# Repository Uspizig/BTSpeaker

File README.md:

# BTSpeaker: The retrofit Board for an cheap Aliexpress Speaker

## Features:

1. **AudioAmplifier MAX98357**: Listen to your favourite Tunes with an Audio Amplifier

2. **I2C Connector for Sensor**: Connect your favourite I2C Sensor board with the embedded 2.54mm connector

3. **LoRa**: Long Range Communication like Meshtastikm, The Thingsnetwork or Helium

4. **Wireless Control**: Untehther your development process with the wireless capabilities. With WiFi, Lora and BLE, this tool allows remote control and data logging. Users can adjust settings and monitor data from a distance, offering a more flexible development experience.

5. **Open Source & Programmable**: As an open-source device, the Device offers unmatched versatility. It is fully programmable, allowing you to tailor its functionality to your specific applications. This customization extends to software and hardware, opening up endless possibilities for creative and efficient project development.

6. **Compact Design**: Designed for convenience, the LoRaCam Board compact and sleek form factor allows for seamless integration into existing setups. Its compatibility with USB PD power sources and inline integration capability minimizes the need for additional equipment or extensive redesign, making it a versatile and user-friendly addition to any development environment.

7. **Eink/Epaper-Display**: Monitor live the current status

8. **LoRa**: Operate the Device in remote areas without Wifi in Standalone mode

9. **3 x RGB LED**: Status LED
## Specifications

### Key Features:
1. **Audio Player**: Play your favorite tunes from SD Card
2. **Web Radio**: Play your favourite tunes from the Web
3. **RGB LEDs** Illuminate your room with fany colors
4. **GYRO** Monitor movements, steps, pedometer

### Future Developments:

AI Detection of movememt and determine if the device shall sent the data via LoRa 

## Testing for Performance

At the heart of BTSpeaker's design is a commitment to reliability and performance. To ensure that SenseLoRaCam stands up to real-world demands, we subjected it to testing under use conditions.

## License

MIT License

Copyright (c) 2025 blue2monster

Permission is hereby granted, free of charge, to any person obtaining a copy
of this software and associated documentation files (the "Software"), to deal
in the Software without restriction, including without limitation the rights
to use, copy, modify, merge, publish, distribute, sublicense, and/or sell
copies of the Software, and to permit persons to whom the Software is
furnished to do so, subject to the following conditions:

The above copyright notice and this permission notice shall be included in all
copies or substantial portions of the Software.

THE SOFTWARE IS PROVIDED "AS IS", WITHOUT WARRANTY OF ANY KIND, EXPRESS OR
IMPLIED, INCLUDING BUT NOT LIMITED TO THE WARRANTIES OF MERCHANTABILITY,
FITNESS FOR A PARTICULAR PURPOSE AND NONINFRINGEMENT. IN NO EVENT SHALL THE
AUTHORS OR COPYRIGHT HOLDERS BE LIABLE FOR ANY CLAIM, DAMAGES OR OTHER
LIABILITY, WHETHER IN AN ACTION OF CONTRACT, TORT OR OTHERWISE, ARISING FROM,
OUT OF OR IN CONNECTION WITH THE SOFTWARE OR THE USE OR OTHER DEALINGS IN THE
SOFTWARE.

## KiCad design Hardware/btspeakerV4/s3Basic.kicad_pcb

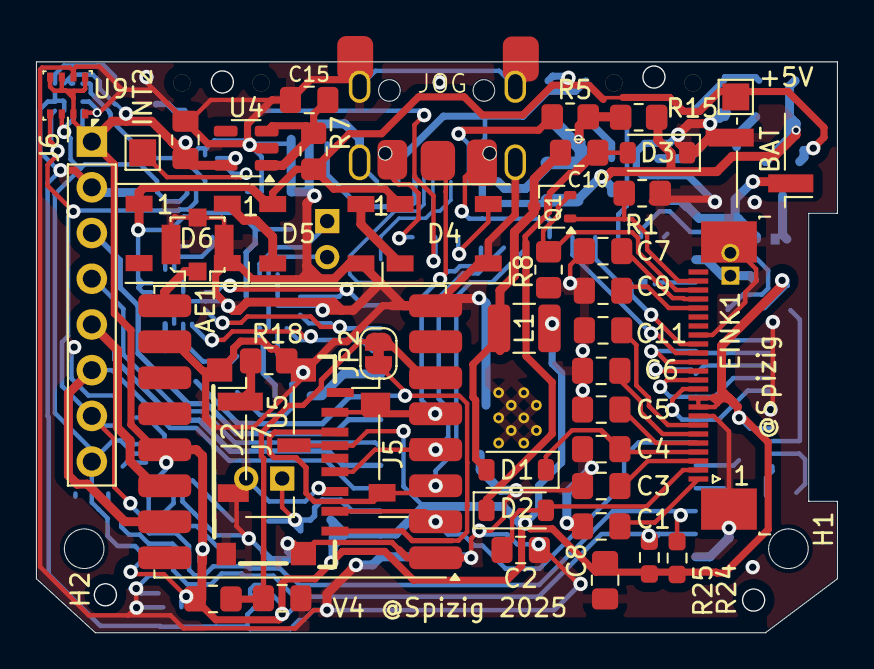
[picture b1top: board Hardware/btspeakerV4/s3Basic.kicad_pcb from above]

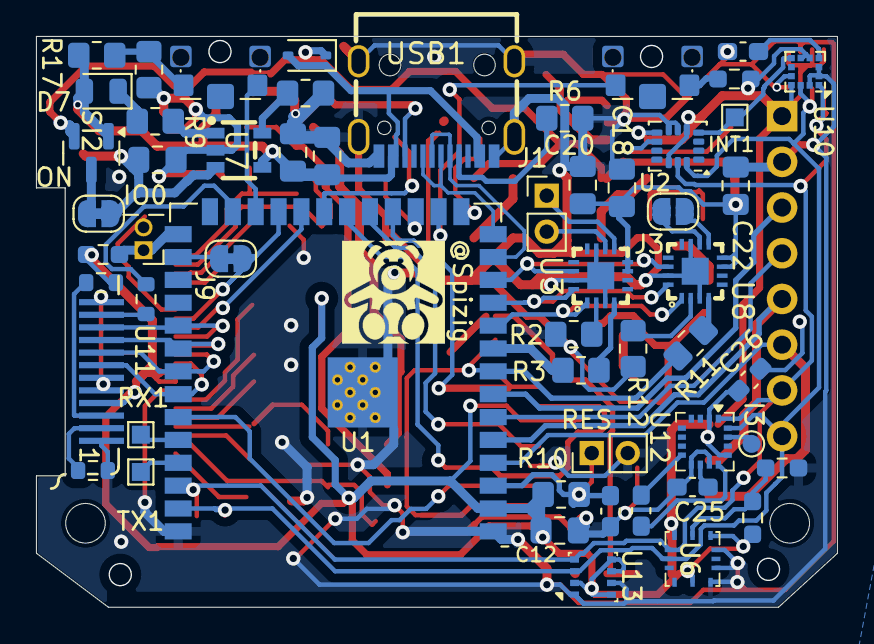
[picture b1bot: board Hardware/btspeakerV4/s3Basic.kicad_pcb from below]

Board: 2 copper layers, 44.5 x 31.7 mm, 103 parts (56 on the bottom side), 85 nets.

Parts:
+5V: TestPoint; TestPoint_Pad_1.5x1.5mm
AE1: Antenna_Shield; U.FL_Molex_MCRF_73412-0110_Vertical
BAT: PWR; PinHeader_1x02_P2.54mm_Vertical_SMD_Pin1Left
C1, C2, C3, C4, C5, C6, C7, C9, C11, C16: 1uF; C_0805_2012Metric_Pad1.18x1.45mm_HandSolder
C8, C17, C18, C19, C20, C22, C23: 100nF; C_0805_2012Metric_Pad1.18x1.45mm_HandSolder
C10, C12, C14, C15: 4.7uF50V; C_0805_2012Metric_Pad1.18x1.45mm_HandSolder
C13, C21, C24, C25, C26: 100nF; C_0603_1608Metric_Pad1.08x0.95mm_HandSolder
D1, D2, D3: MBR0530; D_SOD-123
D4, D5, D6: WS2812B; LED_WS2812B_PLCC4_5.0x5.0mm_P3.2mm
D7: LED; LED_0805_2012Metric
D8: MBR0530; D_SOD-323
EINK1: FPCConn; TE_2-1734839-4_1x24-1MP_P0.5mm_Horizontal
H1, H2: MountingHole; MountingHole_2.2mm_M2
H3: MountingHole; baerklein
I3: TestPoint; TestPoint_Pad_D1.0mm
INT1: TestPoint; TestPoint_Pad_1.0x1.0mm
INT2: TestPoint; TestPoint_Pad_1.5x1.5mm
IO0: Conn_01x02_Pin; PinHeader_1x02_P1.27mm_Vertical
J1: Conn_01x02_Pin; PinHeader_1x02_P2.00mm_Vertical
J2: Micro_SD_Card_Det_US; TF-SMD_XKTF-0803-0
J3: Conn_01x02_Pin; SolderJumper-2_P1.3mm_Open_RoundedPad1.0x1.5mm
J5, J7: Conn_01x03_Pin; PinHeader_1x03_P2.54mm_Vertical_SMD_Pin1Left
J6: Conn_01x08_Pin; PinHeader_1x08_P2.54mm_Vertical
J9: Conn_01x02_Pin; SolderJumper-2_P1.3mm_Bridged_RoundedPad1.0x1.5mm
JOG: jogdial; JogWheel
JP2: SolderJumper_2_Bridged; SolderJumper-2_P1.3mm_Bridged_RoundedPad1.0x1.5mm
L1: 68uH1A; L_1210_3225Metric
ON: Conn_01x02_Pin; SolderJumper-2_P1.3mm_Bridged_RoundedPad1.0x1.5mm
Q1: Si1308; SOT-323_SC-70
R1, R10, R13, R18: 10K; R_0805_2012Metric_Pad1.20x1.40mm_HandSolder
R2, R12, R15, R17: 100K; R_0805_2012Metric_Pad1.20x1.40mm_HandSolder
R3, R9, R14: 1K; R_0805_2012Metric_Pad1.20x1.40mm_HandSolder
R4, R24, R25: 10K; R_0603_1608Metric_Pad0.98x0.95mm_HandSolder
R5, R6: 5k11; R_0805_2012Metric_Pad1.20x1.40mm_HandSolder
R7: 0R; R_0805_2012Metric_Pad1.20x1.40mm_HandSolder
R8: 3R; R_0805_2012Metric_Pad1.20x1.40mm_HandSolder
R11, R19: 300K; R_0805_2012Metric_Pad1.20x1.40mm_HandSolder
R16, R20, R21: 100K; R_0603_1608Metric_Pad0.98x0.95mm_HandSolder
R23: 22; R_0603_1608Metric
R26: 0R; R_0603_1608Metric
R27: N.C.; R_0603_1608Metric
RES: Conn_01x02_Pin; PinHeader_1x02_P2.00mm_Vertical
RX1: TestPoint; TestPoint_Pad_1.0x1.0mm
SI2: SI2301CDS; SOT-23
SW1, SW2: SW_Push; SW_SPST_CK_KMS2xxGP
TX1: TestPoint; TestPoint_Pad_1.0x1.0mm
U1: ESP32-S3-WROOM-1-Espressif; ESP32-S3-WROOM-1
U2: LSM6DS3; LGA-14_3x2.5mm_P0.5mm_LayoutBorder3x4y
U3, U8: TQFN-16_L3.0-W3.0-P0.50-BL-EP1.5
U4: RT9013; SOT-23-5
U5: RFM95W-868S2; HOPERF_RFM9XW_SMD
U6: 4410AI1V; ZMOD4410AI1V
U7: TP4065; SOT-23-5_L3.0-W1.7-P0.95-LS2.8-BR
U9, U13: BME280; Bosch_LGA-8_2.5x2.5mm_P0.65mm_ClockwisePinNumbering
U10: LIS3MDL; LGA-12_2x2mm_P0.5mm
U11: GC9A01_IPS_display; GC9A01_IPS_display_reversed
U12: MMC5883MA; LGA-16_3x3mm_P0.5mm
USB1: KoreanHropartsElecTYPE-C-31-M-12; USB-C_SMD-TYPE-C-31-M-12

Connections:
+3.3VP: C8.2, C12.2, C14.2, C26.1, EINK1.9 (16), EINK1.10 (15), J2.4 (VDD), J6.1, J7.2, L1.2, R4.2, R10.2, R13.2, R16.1, R21.1, R23.2, R24.1, R25.1, U1.2 (3V3), U2.5 (VDDIO), U2.8 (VDD), U2.12 (CS), U4.5 (VOUT), U5.13 (3.3V), U6.5 (VDD), U6.10 (VDDH), U6.12 (VDDIO), U9.2 (CSB), U9.5 (SDO), U9.6 (VDDIO), U9.8 (VDD), U10.5 (Vdd), U10.6 (Vdd_IO), U10.10 (~CS), U11.4 (VDD), U12.2 (VDD), U12.13 (VDDIO), U13.2 (CSB), U13.5 (SDO), U13.6 (VDDIO), U13.8 (VDD)
+5V: C15.2, R7.1, U4.1 (VIN), U4.3 (EN)
+5VD: C16.1, C17.1, D7.2 (A), D8.2 (A), R15.1, R17.1, SI2.1 (G), U7.4 (VCC), USB1.A4 (VBUS), USB1.A9 (VBUS), USB1.B4 (VBUS), USB1.B9 (VBUS)
+BATT: BAT.1, C19.2, ON.2, U7.3 (BAT)
/AUDIO_BCLK: U1.11 (GPIO18/U1RXD/ADC2_CH7/CLK_OUT3), U3.16 (BCLK), U8.16 (BCLK)
/AUDIO_DIN: U1.10 (GPIO17/U1TXD/ADC2_CH6), U3.1 (DIN), U8.1 (DIN)
/AUDIO_LRC: U1.12 (GPIO8/TOUCH8/ADC1_CH7/SUBSPICS1), U3.14 (LRCLK), U8.14 (LRCLK)
/AUDIO_SD: R3.1, U1.9 (GPIO16/U0CTS/ADC2_CH5/XTAL_32K_NH5)
/AUDIO_SD2: J2.8 (DAT1), JP2.1 (A), R11.1, U1.8 (GPIO15/U0RTS/ADC2_CH4/XTAL_32K_P)
/Button1: SW2.1, U1.24 (GPIO47/SPICLK_P/SUBSPICLK_P_DIFF)
/Button2: SW1.2, U1.16 (GPIO46)
/D+: U1.14 (GPIO20/U1CTS/ADC2_CH9/CLK_OUT1/USB_D+), USB1.A6 (DP1), USB1.B6 (DP2)
/D-: U1.13 (GPIO19/U1RTS/ADC2_CH8/CLK_OUT2/USB_D-), USB1.A7 (DN1), USB1.B7 (DN2)
/DISP_RES: R26.2, U1.25 (GPIO48/SPICLK_N/SUBSPICLK_N_DIFF)
/EPD_BU2: J9.1, U1.28 (SPIIO6/GPIO35/FSPID/SUBSPID)
/EPD_BUSY: EINK1.16 (9), J9.2, U1.23 (GPIO21)
/EPD_CLK: EINK1.12 (13), U1.33 (MTDO/GPIO40/CLK_OUT2), U11.8 (~CS)
/EPD_CS: EINK1.13 (12), U1.32 (MTCK/GPIO39/CLK_OUT3/SUBSPICS1), U11.9 (SCK)
/EPD_DC: EINK1.14 (11), U1.31 (GPIO38/FSPIWP/SUBSPIWP), U11.10 (SDI)
/EPD_MOSI: EINK1.11 (14), U1.34 (MTDI/GPIO41/CLK_OUT1), U11.7 (D/C)
/EPD_RST: EINK1.15 (10), U1.22 (GPIO14/TOUCH14/ADC2_CH3/FSPIWP/FSPIDQS/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)
/GPIO1: J6.8, R25.2, U1.39 (GPIO1/TOUCH1/ADC1_CH0), U2.14 (SDA), U6.2 (SDA), U9.3 (SDI), U10.11 (SDA/SDI/SDO), U12.16 (SDA), U13.3 (SDI)
/GPIO2: J6.7, R24.2, U1.38 (GPIO2/TOUCH2/ADC1_CH1), U2.13 (SCL), U6.1 (SCL), U9.4 (SCK), U10.1 (SCL/SPC), U12.1 (SCL), U13.4 (SCK)
/GPIO4: J6.6, U1.4 (GPIO4/TOUCH4/ADC1_CH3), U5.15 (DIO1)
/GPIO5: J6.5, U1.5 (GPIO5/TOUCH5/ADC1_CH4), U5.14 (DIO0)
/GPIO6: J6.4, U1.6 (GPIO6/TOUCH6/ADC1_CH5)
/GPIO7: J6.3, U1.7 (GPIO7/TOUCH7/ADC1_CH6)
/GPIO9: D4.4 (DIN), U1.17 (GPIO9/TOUCH9/ADC1_CH8/FSPIHD/SUBSPIHD)
/INT1: INT1.1, U2.4 (INT1), U10.7 (INT)
/IO0: IO0.1, R4.1, U1.27 (GPIO0/BOOT)
/LORA_CLK: J2.5 (CLK), J5.2, U1.19 (GPIO11/TOUCH11/ADC2_CH0/FSPICS0/FSPIIO4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), U5.4 (SCK)
/LORA_CS: J2.2 (DAT3/CD), J5.1, JOG.2, U1.18 (GPIO10/TOUCH10/ADC1_CH9/FSPICS0/FSPIIO4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), U5.5 (NSS)
/LORA_MISO: J2.7 (DAT0), U1.35 (MTMS/GPIO42), U5.2 (MISO)
/LORA_MOSI: J2.3 (CMD), J5.3, U1.20 (GPIO12/TOUCH11/ADC2_CH0/FSPICS0/FSPIIO4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), U5.3 (MOSI)
/ROT_A: JOG.1, U1.15 (GPIO3/TOUCH3/ADC1_CH2)
/ROT_B: JOG.3, U1.21 (GPIO13/TOUCH13/ADC2_CH2/FSPIQ/FSPIIO7/S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)
/RXD: RX1.1, U1.36 (U0RXD/GPIO44/CLK_OUT2)
/SEL_R: EINK1.22 (3), Q1.2 (S), R8.2
/TXD: TX1.1, U1.37 (U0TXD/GPIO43/CLK_OUT1)
GND: AE1.2 (Shield), BAT.2, C1.1, C2.1, C3.1, C4.1, C5.1, C6.1, C7.1, C8.1, C9.1, C11.1, C12.1, C13.1, C14.1, C15.1, C16.2, C17.2, C18.2, C19.1, C20.2, C21.1, C22.2, C23.1, C25.1, C26.2, D3.1 (K), D4.3 (VSS), D5.3 (VSS), D6.3 (VSS), EINK1.8 (17), EINK1.17 (8), EINK1.MP (26), IO0.2, J2.6 (VSS), J2.10 (SHELL), J2.11 (SHELL), J2.12 (SHELL), J2.13 (SHELL), J6.2, J7.3, JOG.4, R1.2, R2.1, R5.1, R6.1, R8.1, R12.1, R14.2, R15.2, R18.1, R19.1, R20.1, R27.1, RES.2, U1.1 (GND), U1.40 (GND), U1.41 (GND), U2.6 (GND), U2.7 (GND), U3.3 (GND), U3.11 (GND), U3.15 (GND), U3.17 (GND), U4.2 (GND), U5.1 (GND), U5.8 (GND), U5.10 (GND), U6.6 (VSS), U6.7 (VSS), U6.9 (VSS), U7.2 (GND), U8.3 (GND), U8.11 (GND), U8.15 (GND), U8.17 (GND), U9.1 (GND), U9.7 (GND), U10.2 (GND), U10.3 (GND), U10.9 (SDO/SA1), U10.12 (GND), U11.1 (GND), U11.5 (GND), U11.6 (GND), U11.12 (GND), U12.9 (GND), U12.11 (GND), U13.1 (GND), U13.7 (GND), USB1.0, USB1.A1 (GND), USB1.A12 (GND), USB1.B1 (GND), USB1.B12 (GND)
unnamed: AE1.1 (A), U5.9 (ANT)
unnamed: C10.1, D1.2 (A), L1.1, Q1.3 (D)
unnamed: C4.2, D1.1 (K), EINK1.4 (21)
unnamed: C2.2, D2.2 (A), EINK1.2 (23)
unnamed: C10.2, D2.1 (K), D3.2 (A)
unnamed: D4.2 (DOUT), D5.4 (DIN)
unnamed: D5.2 (DOUT), D6.4 (DIN)
unnamed: D7.1 (K), R9.1
unnamed: EINK1.23 (2), Q1.1 (G), R1.1
unnamed: C7.2, EINK1.21 (4)
unnamed: C9.2, EINK1.20 (5)
unnamed: C11.2, EINK1.7 (18)
unnamed: C6.2, EINK1.6 (19)
unnamed: C5.2, EINK1.5 (20)
unnamed: C3.2, EINK1.3 (22)
unnamed: C1.2, EINK1.1 (24)
unnamed: J1.1, U3.9 (OUTP)
unnamed: J1.2, U3.10 (OUTN)
unnamed: J3.1, U8.9 (OUTP)
unnamed: J3.2, U8.10 (OUTN)
unnamed: J7.1, R18.2
unnamed: C23.2, JP2.2 (B), R13.1, U5.6 (RESET)
unnamed: ON.1, SI2.3 (D)
unnamed: R16.2, SW1.1
unnamed: R17.2, R19.2, SW2.2
unnamed: C13.2, R10.1, RES.1, U1.3 (EN)
unnamed: INT2.1, U2.9 (INT2)
unnamed: R2.2, U3.2 (GAIN)
unnamed: R3.2, U3.4 (SD)
unnamed: R20.2, R21.2, U6.11 (RES_N)
unnamed: R9.2, U7.1 (CHRG)
unnamed: R14.1, U7.5 (PROG)
unnamed: R12.2, U8.2 (GAIN)
unnamed: R11.2, U8.4 (SD)
unnamed: C21.2, U10.4 (C1)
unnamed: R23.1, U11.3 (LEDA)
unnamed: R27.2, U11.2 (LEDK)
unnamed: R26.1, U11.11 (~RESET)
unnamed: C24.1, U12.8 (C1)
unnamed: C24.2, U12.12 (C2)
unnamed: C25.2, U12.10 (CAP)
unnamed: I3.1, U12.15 (INT)
unnamed: R6.2, USB1.A5 (CC1)
unnamed: R5.2, USB1.B5 (CC2)
VDC: +5V.1, C18.1, C20.1, C22.1, D4.1 (VDD), D5.1 (VDD), D6.1 (VDD), D8.1 (K), R7.2, SI2.2 (S), U3.7 (VDD), U3.8 (VDD), U8.7 (VDD), U8.8 (VDD)

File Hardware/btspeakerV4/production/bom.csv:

Designator,Footprint,Quantity,Value,LCSC Part #
"+5V, INT2",TestPoint_Pad_1.5x1.5mm,2,TestPoint,
AE1,U.FL_Molex_MCRF_73412-0110_Vertical,1,Antenna_Shield,
BAT,PinHeader_1x02_P2.54mm_Vertical_SMD_Pin1Left,1,PWR,
"C1, C11, C16, C2, C3, C4, C5, C6, C7, C9",0805,10,1uF,
"C10, C12, C14, C15",0805,4,4.7uF50V,
"C13, C21, C24, C25, C26",0603,5,100nF,
"C17, C18, C19, C20, C22, C23, C8",0805,7,100nF,
"D1, D2, D3",D_SOD-123,3,MBR0530,
"D4, D5, D6",LED_WS2812B_PLCC4_5.0x5.0mm_P3.2mm,3,WS2812B,
D7,0805,1,LED,
D8,D_SOD-323,1,MBR0530,
EINK1,TE_2-1734839-4_1x24-1MP_P0.5mm_Horizontal,1,FPCConn,
"H1, H2",MountingHole_2.2mm_M2,2,MountingHole,
I3,TestPoint_Pad_D1.0mm,1,TestPoint,
"INT1, RX, TX",TestPoint_Pad_1.0x1.0mm,3,TestPoint,
IO0,PinHeader_1x02_P1.27mm_Vertical,1,Conn_01x02_Pin,
"J1, RES",PinHeader_1x02_P2.00mm_Vertical,2,Conn_01x02_Pin,
J2,TF-SMD_XKTF-0803-0,1,Micro_SD_Card_Det_US,
J3,SolderJumper-2_P1.3mm_Open_RoundedPad1.0x1.5mm,1,Conn_01x02_Pin,
"J5, J7",PinHeader_1x03_P2.54mm_Vertical_SMD_Pin1Left,2,Conn_01x03_Pin,
J6,PinHeader_1x08_P2.54mm_Vertical,1,Conn_01x08_Pin,
"J9, ON",SolderJumper-2_P1.3mm_Bridged_RoundedPad1.0x1.5mm,2,Conn_01x02_Pin,
JOG,JogWheel,1,jogdial,
JP2,SolderJumper-2_P1.3mm_Bridged_RoundedPad1.0x1.5mm,1,SolderJumper_2_Bridged,
L1,1210,1,68uH1A,
Q1,SOT-323_SC-70,1,Si1308,
"R1, R10, R13, R18",0805,4,10K,
"R11, R19",0805,2,300K,
"R12, R15, R17, R2",0805,4,100K,
"R14, R3, R9",0805,3,1K,
"R16, R20, R21",0603,3,100K,
R23,0603,1,22,
"R24, R25, R4",0603,3,10K,
R26,0603,1,0R,
R27,0603,1,N.C.,
"R5, R6",0805,2,5k11,
R7,0805,1,0R,
R8,0805,1,3R,
SI2,SOT-23,1,SI2301CDS,
"SW1, SW2",SW_SPST_CK_KMS2xxGP,2,SW_Push,
U1,ESP32-S3-WROOM-1,1,ESP32-S3-WROOM-1-Espressif,
U10,LGA-12_2x2mm_P0.5mm,1,LIS3MDL,
U11,GC9A01_IPS_display_reversed,1,GC9A01_IPS_display,
U12,LGA-16_3x3mm_P0.5mm,1,MMC5883MA,
"U13, U9",Bosch_LGA-8_2.5x2.5mm_P0.65mm_ClockwisePinNumbering,2,BME280,
U2,LGA-14_3x2.5mm_P0.5mm_LayoutBorder3x4y,1,LSM6DS3,
"U3, U8",TQFN-16_L3.0-W3.0-P0.50-BL-EP1.5,2,~,
U4,SOT-23-5,1,RT9013,
U5,HOPERF_RFM9XW_SMD,1,RFM95W-868S2,
U6,ZMOD4410AI1V,1,4410AI1V,
U7,SOT-23-5_L3.0-W1.7-P0.95-LS2.8-BR,1,TP4065,
USB,USB-C_SMD-TYPE-C-31-M-12,1,KoreanHropartsElecTYPE-C-31-M-12,

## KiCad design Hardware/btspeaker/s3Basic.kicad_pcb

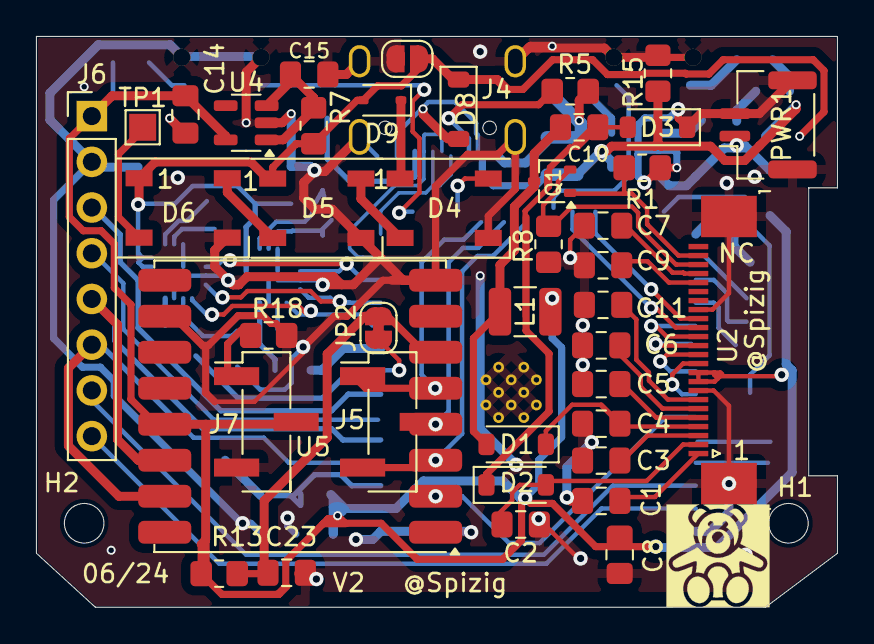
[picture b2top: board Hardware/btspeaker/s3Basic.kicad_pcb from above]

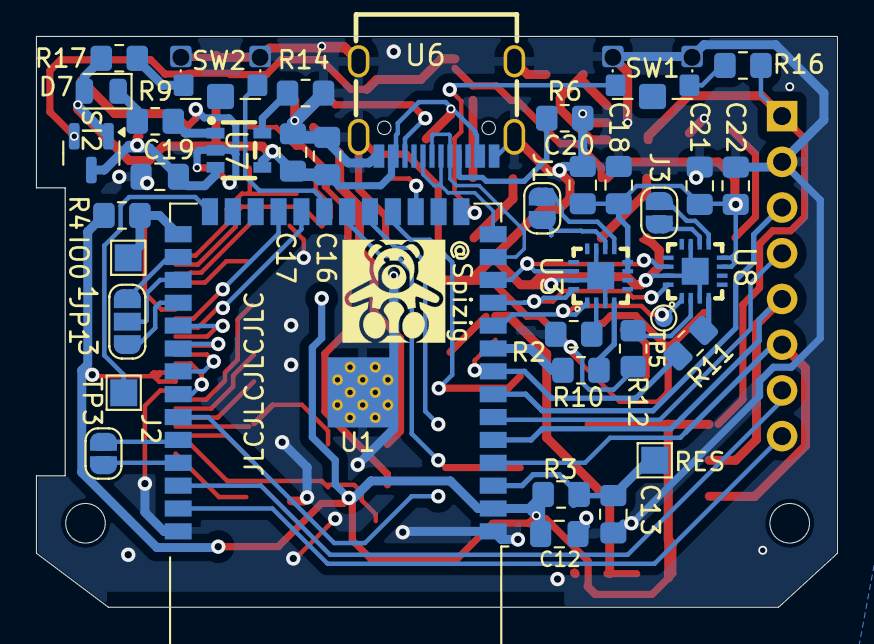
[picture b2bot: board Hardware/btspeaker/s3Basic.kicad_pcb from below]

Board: 2 copper layers, 44.5 x 31.7 mm, 80 parts (37 on the bottom side), 74 nets.

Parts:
C1, C2, C3, C4, C5, C6, C7, C9, C11: 105; C_0805_2012Metric_Pad1.18x1.45mm_HandSolder
C8: 104; C_0805_2012Metric_Pad1.18x1.45mm_HandSolder
C10, C12, C14, C15: 4.7uF50V; C_0805_2012Metric_Pad1.18x1.45mm_HandSolder
C13, C17, C18, C19, C20, C21, C22, C23: 100nF; C_0805_2012Metric_Pad1.18x1.45mm_HandSolder
C16: 1uF; C_0805_2012Metric_Pad1.18x1.45mm_HandSolder
D1, D2, D3, D8: MBR0530; D_SOD-123
D4, D5, D6: WS2812B; LED_WS2812B_PLCC4_5.0x5.0mm_P3.2mm
D7: LED; LED_0805_2012Metric
D9: MBR0530; D_SOD-323
H1, H2: MountingHole; MountingHole_2.2mm_M2
IO0: TestPoint; TestPoint_Pad_1.5x1.5mm
J1, J2, J3, J4: Conn_01x02_Pin; SolderJumper-2_P1.3mm_Open_RoundedPad1.0x1.5mm
J5, J7: Conn_01x03_Pin; PinHeader_1x03_P2.54mm_Vertical_SMD_Pin1Left
J6: Conn_01x08_Pin; PinHeader_1x08_P2.54mm_Vertical
JP1: SolderJumper_3_Open; SolderJumper-3_P1.3mm_Open_RoundedPad1.0x1.5mm_NumberLabels
JP2: SolderJumper_2_Bridged; SolderJumper-2_P1.3mm_Bridged_RoundedPad1.0x1.5mm
L1: 68uH1A; L_1210_3225Metric
PWR1: PWR; JST_GH_SM02B-GHS-TB_1x02-1MP_P1.25mm_Horizontal
Q1: Si1308; SOT-323_SC-70
R1, R3, R4, R13: 10K; R_0805_2012Metric_Pad1.20x1.40mm_HandSolder
R2, R9, R10, R12, R14, R18: 1K; R_0805_2012Metric_Pad1.20x1.40mm_HandSolder
R5, R6: 5k11; R_0805_2012Metric_Pad1.20x1.40mm_HandSolder
R7: 0R; R_0805_2012Metric_Pad1.20x1.40mm_HandSolder
R8: 3R; R_0805_2012Metric_Pad1.20x1.40mm_HandSolder
R11: 210k; R_0805_2012Metric_Pad1.20x1.40mm_HandSolder
R15, R16, R17: 100K; R_0805_2012Metric_Pad1.20x1.40mm_HandSolder
RES: TestPoint; TestPoint_Pad_1.5x1.5mm
SI2: SI2301CDS; SOT-23
SW1, SW2: SW_Push; SW_SPST_CK_KMS2xxGP
TP1, TP3: TestPoint; TestPoint_Pad_1.5x1.5mm
TP5: TestPoint; TestPoint_Pad_D1.0mm
U1: ESP32-S3-WROOM-1-Espressif; ESP32-S3-WROOM-1
U2: FPCConn; TE_2-1734839-4_1x24-1MP_P0.5mm_Horizontal
U3, U8: TQFN-16_L3.0-W3.0-P0.50-BL-EP1.5
U4: RT9013; SOT-23-5
U5: RFM95W-868S2; HOPERF_RFM9XW_SMD
U6: KoreanHropartsElecTYPE-C-31-M-12; USB-C_SMD-TYPE-C-31-M-12
U7: TP4065; SOT-23-5_L3.0-W1.7-P0.95-LS2.8-BR

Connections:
+3.3VP: C8.2, C12.2, C14.2, J6.1, J7.2, L1.2, R3.2, R4.2, R13.2, R16.1, U1.2 (3V3), U2.9 (16), U2.10 (15), U4.5 (VOUT), U5.13 (3.3V)
+5V: C15.2, R7.1, U4.1 (VIN), U4.3 (EN)
+5VD: C16.1, C17.1, D7.2 (A), D8.2 (A), R15.1, R17.1, SI2.1 (G), U6.A4 (VBUS), U6.A9 (VBUS), U6.B4 (VBUS), U6.B9 (VBUS), U7.4 (VCC)
+BATT: C19.2, PWR1.1, SI2.3 (D), U7.3 (BAT)
/AUDIO_BCLK: U1.11 (GPIO18/U1RXD/ADC2_CH7/CLK_OUT3), U3.16 (BCLK), U8.16 (BCLK)
/AUDIO_DIN: TP5.1, U1.10 (GPIO17/U1TXD/ADC2_CH6), U3.1 (DIN), U8.1 (DIN)
/AUDIO_LRC: U1.12 (GPIO8/TOUCH8/ADC1_CH7/SUBSPICS1), U3.14 (LRCLK), U8.14 (LRCLK)
/AUDIO_SD: R10.1, U1.9 (GPIO16/U0CTS/ADC2_CH5/XTAL_32K_NH5)
/AUDIO_SD2: JP2.1 (A), R11.1, U1.8 (GPIO15/U0RTS/ADC2_CH4/XTAL_32K_P)
/Button1: SW2.1, U1.21 (GPIO13/TOUCH13/ADC2_CH2/FSPIQ/FSPIIO7/S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)
/Button2: SW1.2, U1.15 (GPIO3/TOUCH3/ADC1_CH2)
/D+: U1.14 (GPIO20/U1CTS/ADC2_CH9/CLK_OUT1/USB_D+), U6.A6 (DP1), U6.B6 (DP2)
/D-: U1.13 (GPIO19/U1RTS/ADC2_CH8/CLK_OUT2/USB_D-), U6.A7 (DN1), U6.B7 (DN2)
/EPD_BUSY: U1.23 (GPIO21), U2.16 (9)
/EPD_CLK: U1.33 (MTDO/GPIO40/CLK_OUT2), U2.12 (13)
/EPD_CS: U1.32 (MTCK/GPIO39/CLK_OUT3/SUBSPICS1), U2.13 (12)
/EPD_DC: U1.31 (GPIO38/FSPIWP/SUBSPIWP), U2.14 (11)
/EPD_MOSI: U1.34 (MTDI/GPIO41/CLK_OUT1), U2.11 (14)
/EPD_RST: U1.22 (GPIO14/TOUCH14/ADC2_CH3/FSPIWP/FSPIDQS/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), U2.15 (10)
/GPIO1: J6.8, U1.39 (GPIO1/TOUCH1/ADC1_CH0)
/GPIO2: J6.7, U1.38 (GPIO2/TOUCH2/ADC1_CH1)
/GPIO4: J6.6, U1.4 (GPIO4/TOUCH4/ADC1_CH3), U5.15 (DIO1)
/GPIO5: J6.5, U1.5 (GPIO5/TOUCH5/ADC1_CH4), U5.14 (DIO0)
/GPIO6: J6.4, U1.6 (GPIO6/TOUCH6/ADC1_CH5)
/GPIO7: J6.3, U1.7 (GPIO7/TOUCH7/ADC1_CH6)
/GPIO9: D4.4 (DIN), U1.17 (GPIO9/TOUCH9/ADC1_CH8/FSPIHD/SUBSPIHD)
/IO0: IO0.1, R4.1, U1.27 (GPIO0/BOOT)
/LORA_CLK: J5.2, U1.19 (GPIO11/TOUCH11/ADC2_CH0/FSPICS0/FSPIIO4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), U5.4 (SCK)
/LORA_CS: J5.1, U1.18 (GPIO10/TOUCH10/ADC1_CH9/FSPICS0/FSPIIO4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), U5.5 (NSS)
/LORA_MISO: U1.35 (MTMS/GPIO42), U5.2 (MISO)
/LORA_MOSI: J5.3, U1.20 (GPIO12/TOUCH11/ADC2_CH0/FSPICS0/FSPIIO4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), U5.3 (MOSI)
/RXD: J2.2, U1.36 (U0RXD/GPIO44/CLK_OUT2)
/SEL_R: Q1.2 (S), R8.2, U2.22 (3)
/TXD: J2.1, U1.37 (U0TXD/GPIO43/CLK_OUT1)
GND: C1.1, C2.1, C3.1, C4.1, C5.1, C6.1, C7.1, C8.1, C9.1, C11.1, C12.1, C13.1, C14.1, C15.1, C16.2, C17.2, C18.2, C19.1, C20.2, C21.2, C22.2, C23.1, D3.1 (K), D4.3 (VSS), D5.3 (VSS), D6.3 (VSS), J4.2, J6.2, J7.3, PWR1.2, PWR1.MP, R1.2, R2.1, R5.1, R6.1, R8.1, R12.1, R14.2, R15.2, R18.1, SW1.SH, SW2.SH, U1.1 (GND), U1.40 (GND), U1.41 (GND), U2.8 (17), U2.17 (8), U2.MP (25), U3.3 (GND), U3.11 (GND), U3.15 (GND), U3.17 (GND), U4.2 (GND), U5.1 (GND), U5.8 (GND), U5.10 (GND), U6.0, U6.A1 (GND), U6.A12 (GND), U6.B1 (GND), U6.B12 (GND), U7.2 (GND), U8.3 (GND), U8.11 (GND), U8.15 (GND), U8.17 (GND)
unnamed: C10.1, D1.2 (A), L1.1, Q1.3 (D)
unnamed: C4.2, D1.1 (K), U2.4 (21)
unnamed: C2.2, D2.2 (A), U2.2 (23)
unnamed: C10.2, D2.1 (K), D3.2 (A)
unnamed: D4.2 (DOUT), D5.4 (DIN)
unnamed: D4.1 (VDD), D9.1 (K)
unnamed: D5.2 (DOUT), D6.4 (DIN)
unnamed: D6.2 (DOUT), TP1.1
unnamed: D7.1 (K), R9.1
unnamed: J1.1, U3.9 (OUTP)
unnamed: J1.2, U3.10 (OUTN)
unnamed: J3.1, U8.9 (OUTP)
unnamed: J3.2, U8.10 (OUTN)
unnamed: J7.1, R18.2
unnamed: JP1.1 (A), U1.28 (SPIIO6/GPIO35/FSPID/SUBSPID)
unnamed: JP1.3 (B), U1.30 (SPIDQS/GPIO37/FSPIQ/SUBSPIQ)
unnamed: JP1.2 (C), U1.29 (SPIIO7/GPIO36/FSPICLK/SUBSPICLK)
unnamed: C23.2, JP2.2 (B), R13.1, U5.6 (RESET)
unnamed: Q1.1 (G), R1.1, U2.23 (2)
unnamed: R16.2, SW1.1
unnamed: R17.2, SW2.2
unnamed: C13.2, R3.1, RES.1, U1.3 (EN)
unnamed: TP3.1, U1.26 (GPIO45)
unnamed: C7.2, U2.21 (4)
unnamed: C9.2, U2.20 (5)
unnamed: C11.2, U2.7 (18)
unnamed: C6.2, U2.6 (19)
unnamed: C5.2, U2.5 (20)
unnamed: C3.2, U2.3 (22)
unnamed: C1.2, U2.1 (24)
unnamed: R2.2, U3.2 (GAIN)
unnamed: R10.2, U3.4 (SD)
unnamed: R6.2, U6.A5 (CC1)
unnamed: R5.2, U6.B5 (CC2)
unnamed: R9.2, U7.1 (CHRG)
unnamed: R14.1, U7.5 (PROG)
unnamed: R12.2, U8.2 (GAIN)
unnamed: R11.2, U8.4 (SD)
VDC: C18.1, C20.1, C21.1, C22.1, D5.1 (VDD), D6.1 (VDD), D8.1 (K), D9.2 (A), J4.1, R7.2, SI2.2 (S), U3.7 (VDD), U3.8 (VDD), U8.7 (VDD), U8.8 (VDD)
